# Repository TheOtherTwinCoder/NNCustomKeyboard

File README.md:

[Sponsored by AIVON](https://www.aivon.com/?code=K7)

# NNCustomKeyboard
I love keyboards, but they're not all that great - so let me make my own one something custom, so it's mine and something useful, so it's more practical than a traditional one!

## Look here first!

Here's my Github's sitemap:
3D Files - includes 3D file of PCB (STEP and an image), and its case

Production - includes Gerber Files, BOM, AND PNP/CPL files for PCB Fabrication

Projectfiles - includes .kicad_pcb, .kicad_sch, and .kicad_pro files to open PCB in KiCad

Links (MD file) - includes resources to build this project

README (MD file) - includes images of the PCB, the CSV file of BOM, and Assembly Instructions!

Thank you, Hack Club, AMD, Blueprint, and AIVON!

## Onshape Link

https://cad.onshape.com/documents/c9928b6a9f4ef1bbd20ca445/w/38d45bd75b935af33784f8b5/e/9c69ae00eee7f366adcabbe1?renderMode=0&uiState=69c0b4cf9a5accdf55e440de

## Full Assembly

## The V2 PCB:

## The PCB Schematic:

## Wiring Schematic

## BOM

| Items | Cost | Links | 
| :---: | :---: | :--- |
| Alpha Keys | $2.77 | (https://www.aliexpress.us/item/3256805792312994.html?spm=a2g0o.productlist.main.12.73d47e81v9eLzK&algo_pvid=c15d0a88-20ab-49d7-9c50-cfdaf69e2e98&algo_exp_id=c15d0a88-20ab-49d7-9c50-cfdaf69e2e98-11&pdp_ext_f=%7B%22order%22%3A%22592%22%2C%22spu_best_type%22%3A%22price%22%2C%22eval%22%3A%221%22%2C%22fromPage%22%3A%22search%22%7D&pdp_npi=6%40dis%21USD%2132.73%217.77%21%21%21224.15%2153.17%21%402101dedf17741192468633377e1610%2112000035146888338%21sea%21US%210%21ABX%211%210%21n_tag%3A-29910%3Bd%3Ad098110%3Bm03_new_user%3A-29895%3BpisId%3A5000000197827646&curPageLogUid=56gUHibOIKh2&utparam-url=scene%3Asearch%7Cquery_from%3A%7Cx_object_id%3A1005005978627746%7C_p_origin_prod%3A) |
| PCB | $39 | Order using Gerber Files in the production folder :), this is a JLCPCB estimate, not including shipping. |
| Nice-Nano | $25 | https://typeractive.xyz/products/nice-nano?utm_source=nicekeyboards&utm_medium=referral&utm_campaign=find-a-store |
| Battery | $8 | https://t.ly/81SML |
| Switches | $30 | https://mechanicalkeyboards.com/checkouts/cn/hWNA2r5NHFXzy1tke3oyGLrU/en/information?_r=AQABIg-5BnWXsXSk4_bNypzt72TOds3C857VtIc9BUQPFP0&auto_redirect=false&edge_redirect=true&skip_shop_pay=true|
| Stabilizers | $1 | https://www.keychron.com/products/keychron-gold-plated-pcb-mounted-stabilizer-set?variant=40142423162969&country=US&currency=USD&utm_medium=product_sync&utm_source=google&utm_content=sag_organic&utm_campaign=sag_organic&srsltid=AfmBOopGC2sEL_ogdcSOZLuLDr0binjVVVFys3JigTozS6elob_414EHnZQ |
| Grand Total | $138 | Submitting for review on Mar 21st!!! :) |

## Assembly

1. Since PCBA already assembled the diodes, we can skip this step. However, if no PCBA, solder on the diodes manually.
2. Solder on the AliExpress switches (found in the BOM).
3. Solder on Nice!Nano (BOM), and solder battery (BOM) to B+ and B- pins.
4. 3D Print the Case, located in STEP3D
5. Take the assembled PCB and slot it into the case
6. Solder on the rgb controller to the nice!nano, and the light strip to the controller.
7. Follow the instructions in [this video](https://www.youtube.com/watch?v=O_urj-rF3bQ)
8. That's it :)

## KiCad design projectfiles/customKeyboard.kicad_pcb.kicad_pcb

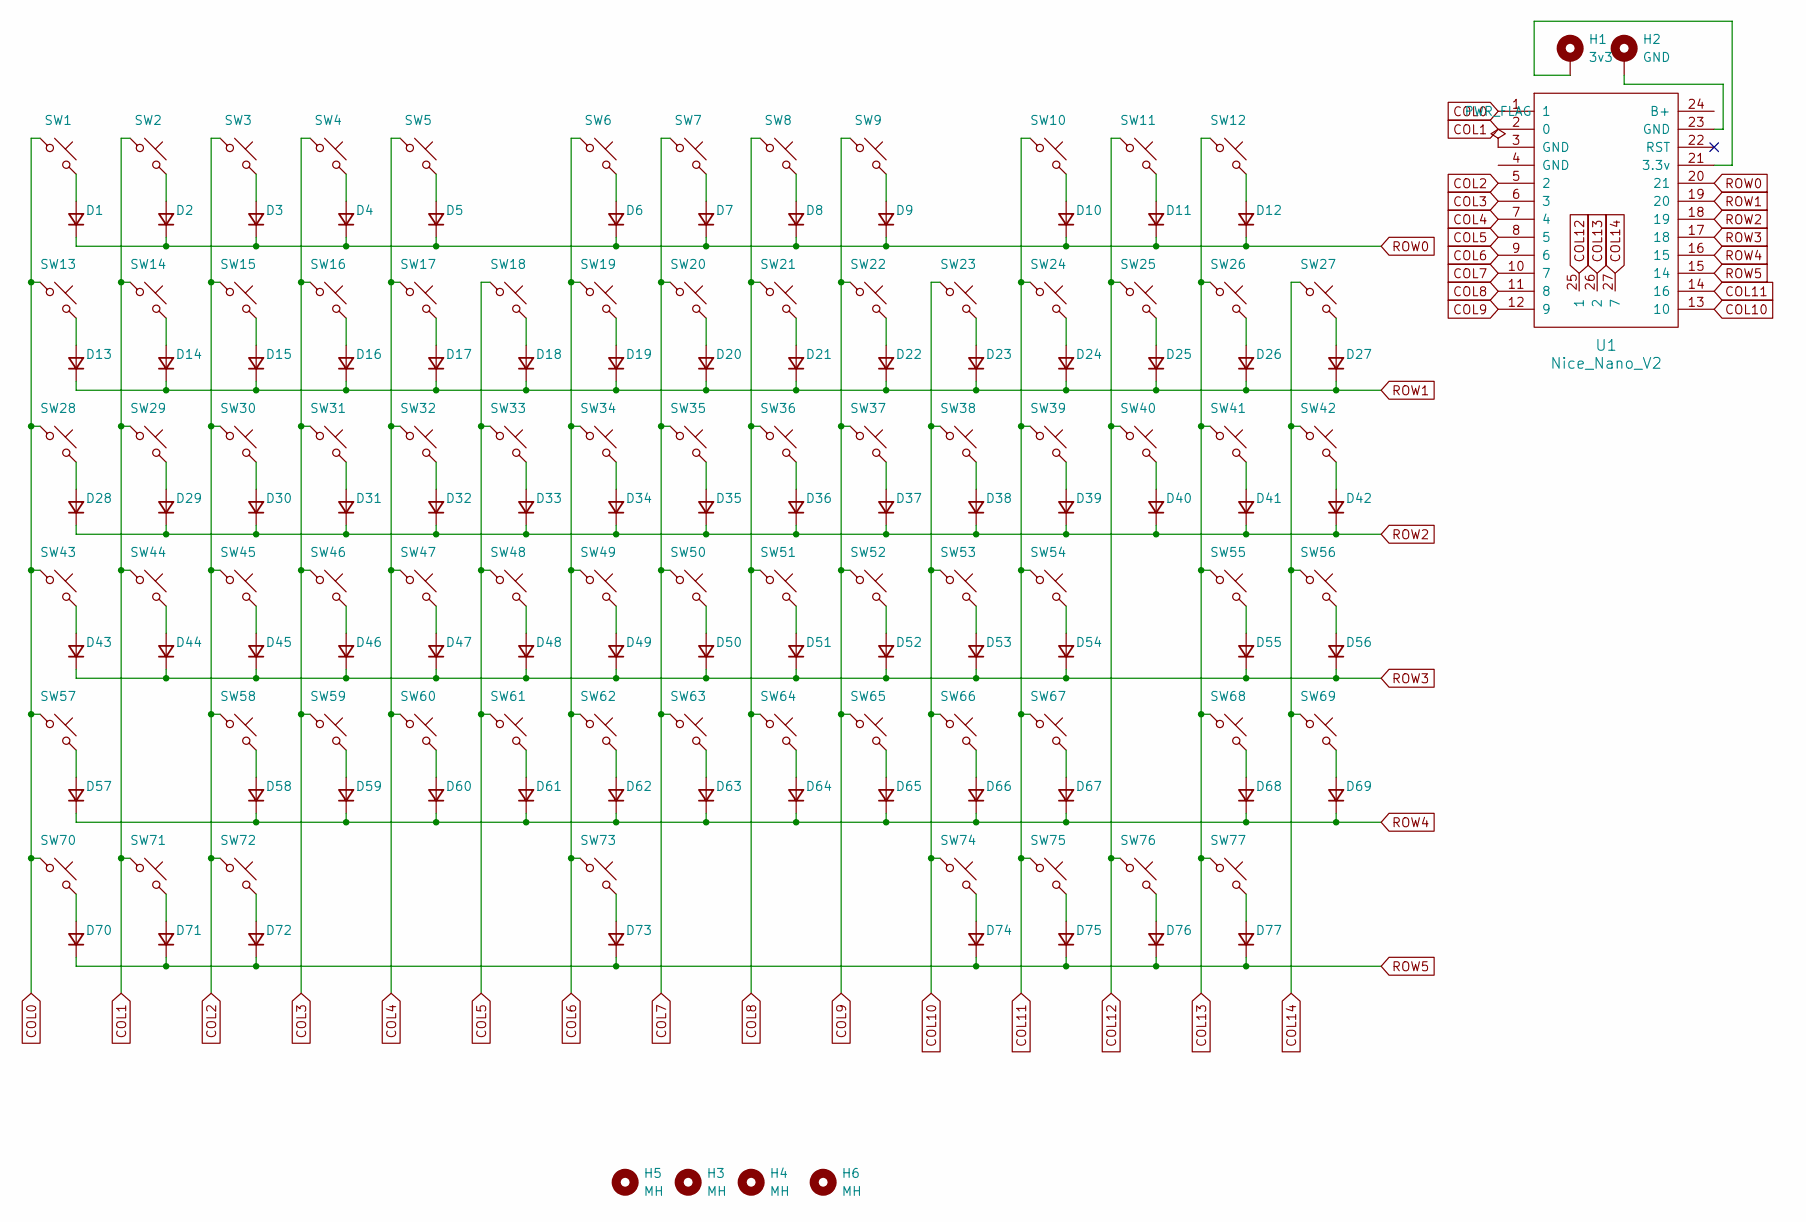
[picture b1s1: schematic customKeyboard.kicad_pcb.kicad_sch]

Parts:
D1, D2, D3, D4, D5, D6, D7, D8, D9, D10, D11, D12, D13, D14, D15, D16, D17, D18, D19, D20, D21, D22, D23, D24, D25, D26, D27, D28, D29, D30, D31, D32, D33, D34, D35, D36, D37, D38, D39, D40, D41, D42, D43, D44, D45, D46, D47, D48, D49, D50, D51, D52, D53, D54, D55, D56, D57, D58, D59, D60, D61, D62, D63, D64, D65, D66, D67, D68, D69, D70, D71, D72, D73, D74, D75, D76, D77: D; D_SOD-123
H1: 3v3; MountingHole_2.2mm_M2
H2: GND; MountingHole_2.2mm_M2
H3, H4, H5, H6: MH; MountingHole_2.2mm_M2
SW1, SW2, SW3, SW4, SW5, SW6, SW7, SW8, SW9, SW10, SW11, SW12, SW13, SW14, SW15, SW16, SW17, SW18, SW19, SW20, SW21, SW22, SW23, SW24, SW25, SW27, SW29, SW30, SW31, SW32, SW33, SW34, SW35, SW36, SW37, SW38, SW39, SW40, SW42, SW44, SW45, SW46, SW47, SW48, SW49, SW50, SW51, SW52, SW53, SW54, SW56, SW58, SW59, SW60, SW61, SW62, SW63, SW64, SW65, SW66, SW67, SW69: SW_Push; SW_Cherry_MX_PCB_1.00u
SW26: SW_Push; SW_Cherry_MX_PCB_2.00u
SW28, SW41: SW_Push; SW_Cherry_MX_PCB_1.50u
SW43: SW_Push; SW_Cherry_MX_PCB_1.75u
SW55, SW57: SW_Push; SW_Cherry_MX_PCB_2.25u
SW68: SW_Push; SW_Cherry_MX_PCB_2.75u
SW70, SW71, SW72, SW74, SW75, SW76, SW77: SW_Push; SW_Cherry_MX_PCB_1.25u
SW73: SW_Push; SW_Cherry_MX_PCB_6.25u
U1: Nice_Nano_V2

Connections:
COL0: SW1.1, SW13.1, SW28.1, SW43.1, SW57.1, SW70.1, U1.1
COL1: SW2.1, SW14.1, SW29.1, SW44.1, SW71.1, U1.2 (0)
COL2: SW3.1, SW15.1, SW30.1, SW45.1, SW58.1, SW72.1, U1.5 (2)
COL3: SW4.1, SW16.1, SW31.1, SW46.1, SW59.1, U1.6 (3)
COL4: SW5.1, SW17.1, SW32.1, SW47.1, SW60.1, U1.7 (4)
COL5: SW18.1, SW33.1, SW48.1, SW61.1, U1.8 (5)
COL6: SW6.1, SW19.1, SW34.1, SW49.1, SW62.1, SW73.1, U1.9 (6)
COL7: SW7.1, SW20.1, SW35.1, SW50.1, SW63.1, U1.10 (7)
COL8: SW8.1, SW21.1, SW36.1, SW51.1, SW64.1, U1.11 (8)
COL9: SW9.1, SW22.1, SW37.1, SW52.1, SW65.1, U1.12 (9)
COL10: SW23.1, SW38.1, SW53.1, SW66.1, SW74.1, U1.13 (10)
COL11: SW10.1, SW24.1, SW39.1, SW54.1, SW67.1, SW75.1, U1.14 (16)
COL12: SW11.1, SW25.1, SW40.1, SW76.1, U1.25 (1)
COL13: SW12.1, SW26.1, SW41.1, SW55.1, SW68.1, SW77.1, U1.26 (2)
COL14: SW27.1, SW42.1, SW56.1, SW69.1, U1.27 (7)
unnamed: D1.2 (A), SW1.2
unnamed: D2.2 (A), SW2.2
unnamed: D3.2 (A), SW3.2
unnamed: D4.2 (A), SW4.2
unnamed: D5.2 (A), SW5.2
unnamed: D6.2 (A), SW6.2
unnamed: D7.2 (A), SW7.2
unnamed: D8.2 (A), SW8.2
unnamed: D9.2 (A), SW9.2
unnamed: D10.2 (A), SW10.2
unnamed: D11.2 (A), SW11.2
unnamed: D12.2 (A), SW12.2
unnamed: D13.2 (A), SW13.2
unnamed: D14.2 (A), SW14.2
unnamed: D15.2 (A), SW15.2
unnamed: D16.2 (A), SW16.2
unnamed: D17.2 (A), SW17.2
unnamed: D18.2 (A), SW18.2
unnamed: D19.2 (A), SW19.2
unnamed: D20.2 (A), SW20.2
unnamed: D21.2 (A), SW21.2
unnamed: D22.2 (A), SW22.2
unnamed: D23.2 (A), SW23.2
unnamed: D24.2 (A), SW24.2
unnamed: D25.2 (A), SW25.2
unnamed: D26.2 (A), SW26.2
unnamed: D27.2 (A), SW27.2
unnamed: D28.2 (A), SW28.2
unnamed: D29.2 (A), SW29.2
unnamed: D30.2 (A), SW30.2
unnamed: D31.2 (A), SW31.2
unnamed: D32.2 (A), SW32.2
unnamed: D33.2 (A), SW33.2
unnamed: D34.2 (A), SW34.2
unnamed: D35.2 (A), SW35.2
unnamed: D36.2 (A), SW36.2
unnamed: D37.2 (A), SW37.2
unnamed: D38.2 (A), SW38.2
unnamed: D39.2 (A), SW39.2
unnamed: D40.2 (A), SW40.2
unnamed: D41.2 (A), SW41.2
unnamed: D42.2 (A), SW42.2
unnamed: D43.2 (A), SW43.2
unnamed: D44.2 (A), SW44.2
unnamed: D45.2 (A), SW45.2
unnamed: D46.2 (A), SW46.2
unnamed: D47.2 (A), SW47.2
unnamed: D48.2 (A), SW48.2
unnamed: D49.2 (A), SW49.2
unnamed: D50.2 (A), SW50.2
unnamed: D51.2 (A), SW51.2
unnamed: D52.2 (A), SW52.2
unnamed: D53.2 (A), SW53.2
unnamed: D54.2 (A), SW54.2
unnamed: D55.2 (A), SW55.2
unnamed: D56.2 (A), SW56.2
unnamed: D57.2 (A), SW57.2
unnamed: D58.2 (A), SW58.2
unnamed: D59.2 (A), SW59.2
unnamed: D60.2 (A), SW60.2
unnamed: D61.2 (A), SW61.2
unnamed: D62.2 (A), SW62.2
unnamed: D63.2 (A), SW63.2
unnamed: D64.2 (A), SW64.2
unnamed: D65.2 (A), SW65.2
unnamed: D66.2 (A), SW66.2
unnamed: D67.2 (A), SW67.2
unnamed: D68.2 (A), SW68.2
unnamed: D69.2 (A), SW69.2
unnamed: D70.2 (A), SW70.2
unnamed: D71.2 (A), SW71.2
unnamed: D72.2 (A), SW72.2
unnamed: D73.2 (A), SW73.2
unnamed: D74.2 (A), SW74.2
unnamed: D75.2 (A), SW75.2
unnamed: D76.2 (A), SW76.2
unnamed: D77.2 (A), SW77.2
unnamed: H2.1, U1.23 (GND)
unnamed: H1.1, U1.21 (3.3v)
ROW0: D1.1 (K), D2.1 (K), D3.1 (K), D4.1 (K), D5.1 (K), D6.1 (K), D7.1 (K), D8.1 (K), D9.1 (K), D10.1 (K), D11.1 (K), D12.1 (K), U1.20 (21)
ROW1: D13.1 (K), D14.1 (K), D15.1 (K), D16.1 (K), D17.1 (K), D18.1 (K), D19.1 (K), D20.1 (K), D21.1 (K), D22.1 (K), D23.1 (K), D24.1 (K), D25.1 (K), D26.1 (K), D27.1 (K), U1.19 (20)
ROW2: D28.1 (K), D29.1 (K), D30.1 (K), D31.1 (K), D32.1 (K), D33.1 (K), D34.1 (K), D35.1 (K), D36.1 (K), D37.1 (K), D38.1 (K), D39.1 (K), D40.1 (K), D41.1 (K), D42.1 (K), U1.18 (19)
ROW3: D43.1 (K), D44.1 (K), D45.1 (K), D46.1 (K), D47.1 (K), D48.1 (K), D49.1 (K), D50.1 (K), D51.1 (K), D52.1 (K), D53.1 (K), D54.1 (K), D55.1 (K), D56.1 (K), U1.17 (18)
ROW4: D57.1 (K), D58.1 (K), D59.1 (K), D60.1 (K), D61.1 (K), D62.1 (K), D63.1 (K), D64.1 (K), D65.1 (K), D66.1 (K), D67.1 (K), D68.1 (K), D69.1 (K), U1.16 (15)
ROW5: D70.1 (K), D71.1 (K), D72.1 (K), D73.1 (K), D74.1 (K), D75.1 (K), D76.1 (K), D77.1 (K), U1.15 (14)

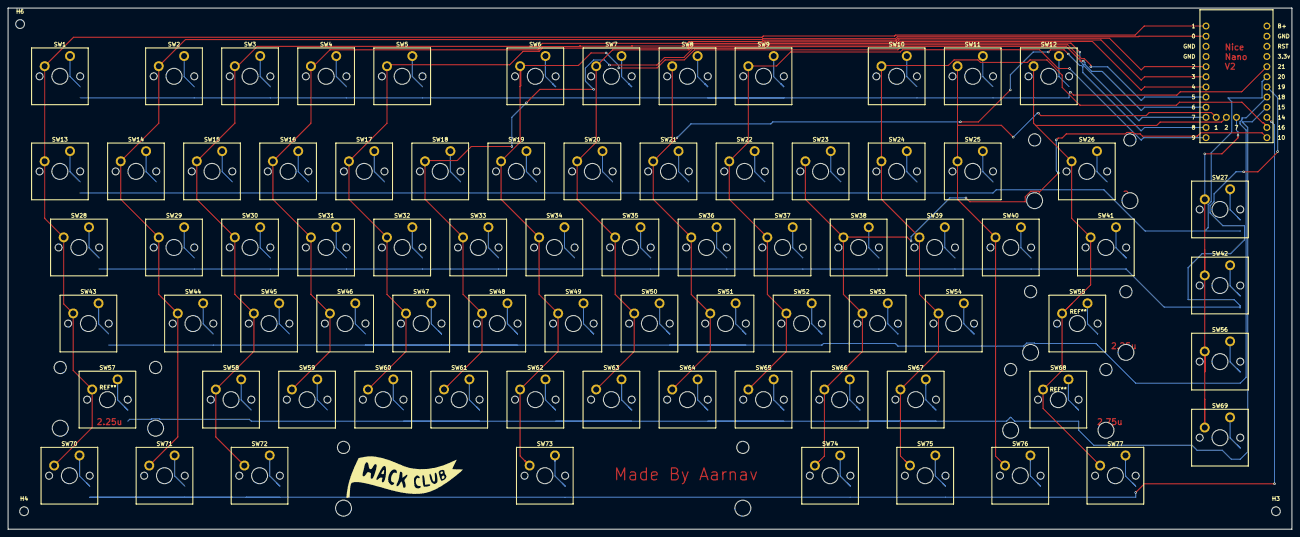
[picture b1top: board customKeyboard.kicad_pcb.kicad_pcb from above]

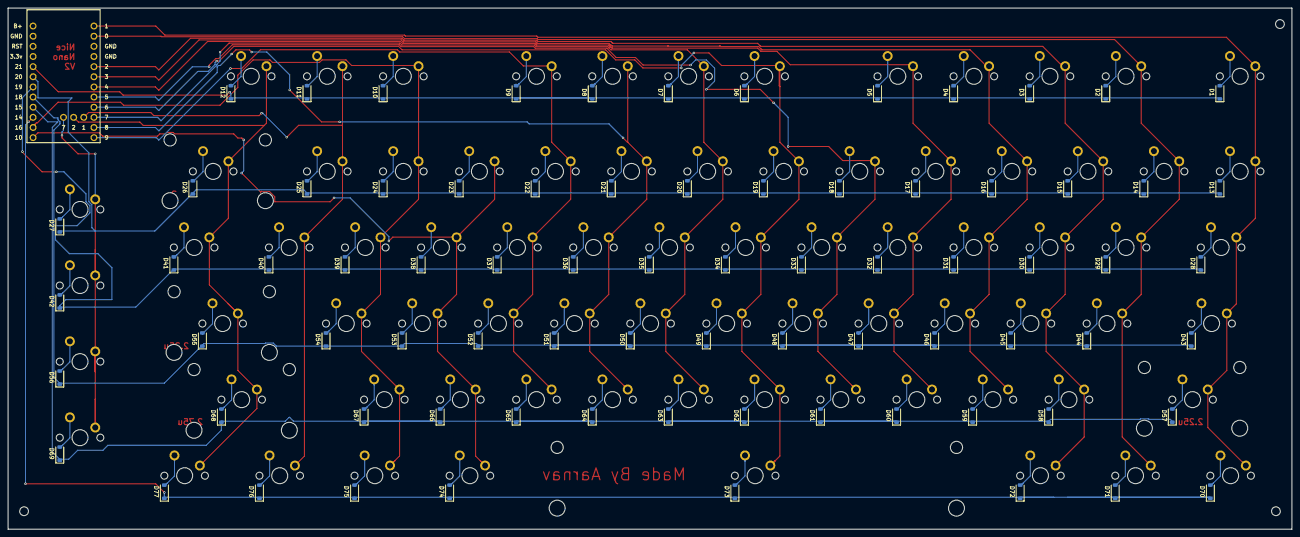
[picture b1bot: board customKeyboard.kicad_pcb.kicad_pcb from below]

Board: 2 copper layers, 321.5 x 130.5 mm, 158 parts (77 on the bottom side), 98 nets.

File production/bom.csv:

Designator,Footprint,Quantity,Value,LCSC Part #
"D1, D10, D11, D12, D13, D14, D15, D16, D17, D18, D19, D2, D20, D21, D22, D23, D24, D25, D26, D27, D28, D29, D3, D30, D31, D32, D33, D34, D35, D36, D37, D38, D39, D4, D40, D41, D42, D43, D44, D45, D46, D47, D48, D49, D5, D50, D51, D52, D53, D54, D55, D56, D57, D58, D59, D6, D60, D61, D62, D63, D64, D65, D66, D67, D68, D69, D7, D70, D71, D72, D73, D74, D75, D76, D77, D8, D9",D_SOD-123F,77,D,
"SW1, SW10, SW11, SW12, SW13, SW14, SW15, SW16, SW17, SW18, SW19, SW2, SW20, SW21, SW22, SW23, SW24, SW25, SW27, SW29, SW3, SW30, SW31, SW32, SW33, SW34, SW35, SW36, SW37, SW38, SW39, SW4, SW40, SW42, SW44, SW45, SW46, SW47, SW48, SW49, SW5, SW50, SW51, SW52, SW53, SW54, SW56, SW58, SW59, SW6, SW60, SW61, SW62, SW63, SW64, SW65, SW66, SW67, SW69, SW7, SW8, SW9",SW_Cherry_MX_PCB_1.00u,62,SW_Push,
SW26,SW_Cherry_MX_PCB_2.00u,1,SW_Push,
"SW28, SW41",SW_Cherry_MX_PCB_1.50u,2,SW_Push,
SW43,SW_Cherry_MX_PCB_1.75u,1,SW_Push,
"SW55, SW57",SW_Cherry_MX_PCB_2.25u,2,SW_Push,
SW68,SW_Cherry_MX_PCB_2.75u,1,SW_Push,
"SW70, SW71, SW72, SW74, SW75, SW76, SW77",SW_Cherry_MX_PCB_1.25u,7,SW_Push,
SW73,SW_Cherry_MX_PCB_6.25u,1,SW_Push,
U1,Nice_Nano_V2,1,Nice_Nano_V2,

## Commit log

2026-03-16 Create new folder
2026-03-16 Rename customKeyboard.kicad_pcb.kicad_pcb to projectfiles/customKeyboard.kicad_pcb.kicad_pcb
2026-03-16 Rename customKeyboard.kicad_pcb.kicad_pro to projectfiles/customKeyboard.kicad_pcb.kicad_pro
2026-03-16 Rename customKeyboard.kicad_pcb.kicad_sch to projectfiles/customKeyboard.kicad_pcb.kicad_sch
2026-03-16 Create t
2026-03-16 Rename customKeyboard.kicad_pcb.step to STEP3D/customKeyboard.kicad_pcb.step
2026-03-16 Create Test
2026-03-21 New Case
2026-03-21 PCB 3D File Image
2026-03-21 Adding Assembly + Renames
2026-03-21 NewCommit
2026-03-22 Mar21
2026-03-22 New3DFIles
2026-03-22 NewPlate
